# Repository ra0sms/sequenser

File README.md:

# Sequencer

More information - https://ra0sms.com/sequencer-2/

It works in two modes:

1. PA BIAS mode (`MODE` jumper is opened)

2. LNA mode (`MODE` jumper is closed)

--------------------------------------------------------------
PCB dimension: 70*45mm

Consumption current: 30mA

Switch current: up to 1A

### Schematic

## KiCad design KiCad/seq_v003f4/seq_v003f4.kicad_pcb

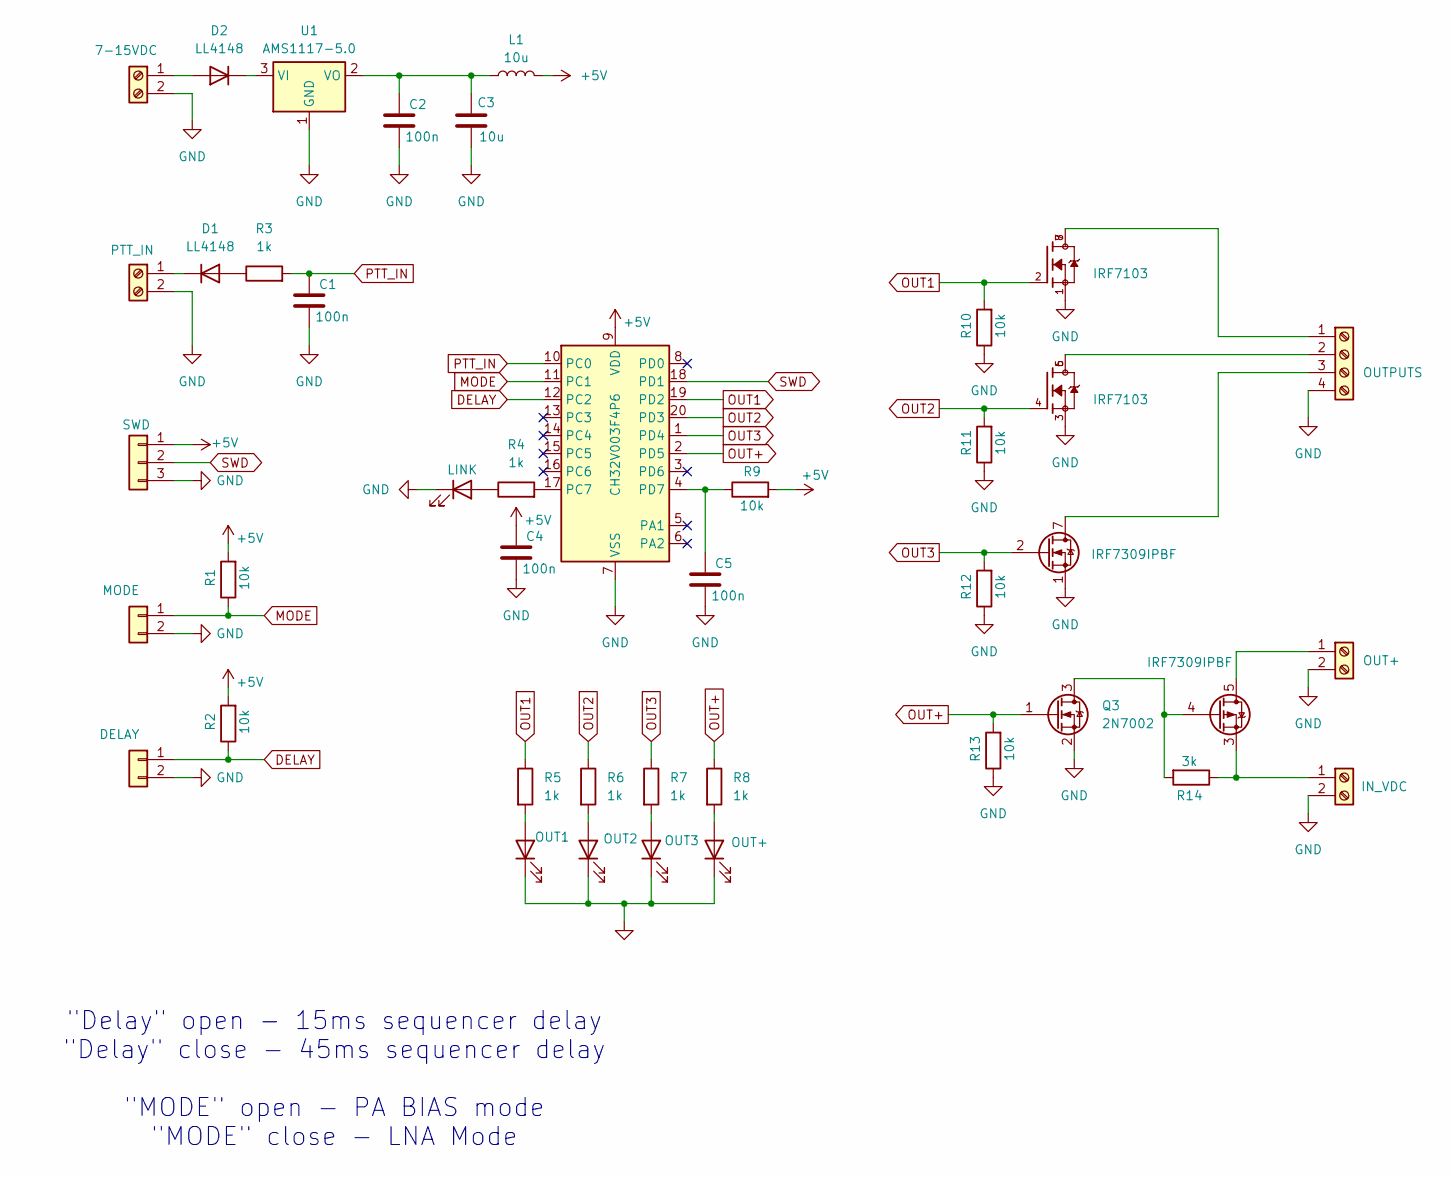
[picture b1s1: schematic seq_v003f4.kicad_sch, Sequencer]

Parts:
C1, C2, C4, C5: 100n; C_1206_3216Metric_Pad1.33x1.80mm_HandSolder
C3: 10u; C_1206_3216Metric_Pad1.33x1.80mm_HandSolder
D1, D2: LL4148; D_MiniMELF
D3: LINK; LED_1206_3216Metric
D4: OUT1; LED_1206_3216Metric
D5: OUT2; LED_1206_3216Metric
D6: OUT3; LED_1206_3216Metric
D7: OUT+; LED_1206_3216Metric
J1: 7-15VDC; TerminalBlock_MetzConnect_Type055_RT01502HDWU_1x02_P5.00mm_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
J2: PTT_IN; TerminalBlock_MetzConnect_Type055_RT01502HDWU_1x02_P5.00mm_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
J3: SWD; PinSocket_1x03_P2.54mm_Vertical
J4: MODE; PinHeader_1x02_P2.54mm_Vertical
J5: DELAY; PinHeader_1x02_P2.54mm_Vertical
J6: OUTPUTS; TerminalBlock_MetzConnect_Type055_RT01504HDWU_1x04_P5.00mm_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
J7: OUT+; TerminalBlock_MetzConnect_Type055_RT01502HDWU_1x02_P5.00mm_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
J8: IN_VDC; TerminalBlock_MetzConnect_Type055_RT01502HDWU_1x02_P5.00mm_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
L1: 10u; L_1206_3216Metric
Q1: IRF7103; SOIC-8_3.9x4.9mm_P1.27mm; PARTREV 02/09/10
Q2: IRF7309IPBF; SOIC-8_3.9x4.9mm_P1.27mm
Q3: 2N7002; SOT-23
R1, R2, R9, R10, R11, R12, R13: 10k; R_1206_3216Metric
R3, R4, R5, R6, R7, R8: 1k; R_1206_3216Metric
R14: 3k; R_1206_3216Metric
U1: AMS1117-5.0; SOT-223-3_TabPin2
U2: CH32V003F4P6; TSSOP-20_4.4x6.5mm_P0.65mm

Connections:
+5V: C4.1, J3.1, L1.2, R1.2, R2.2, R9.2, U2.9 (VDD)
DELAY: J5.1, R2.1, U2.12 (PC2)
GND: C1.2, C2.2, C3.2, C4.2, C5.2, D3.1 (K), D4.1 (K), D5.1 (K), D6.1 (K), D7.1 (K), J1.2, J2.2, J3.3, J4.2, J5.2, J6.4, J7.2, J8.2, Q1.1, Q1.3, Q2.1 (S), Q3.2 (S), R10.1, R11.1, R12.1, R13.1, U1.1 (GND), U2.7 (VSS)
MODE: J4.1, R1.1, U2.11 (PC1)
unnamed: D1.2 (A), R3.1
unnamed: D1.1 (K), J2.1
unnamed: D2.2 (A), J1.1
unnamed: D2.1 (K), U1.3 (VI)
unnamed: D3.2 (A), R4.1
unnamed: D4.2 (A), R5.2
unnamed: D5.2 (A), R6.2
unnamed: D6.2 (A), R7.2
unnamed: D7.2 (A), R8.2
unnamed: J6.1, Q1.7, Q1.8
unnamed: J6.2, Q1.5, Q1.6
unnamed: J6.3, Q2.7 (D), Q2.8 (D)
unnamed: J7.1, Q2.5 (D), Q2.6 (D)
unnamed: J8.1, Q2.3 (1), R14.1
unnamed: Q2.4 (G), Q3.3 (D), R14.2
unnamed: C2.1, C3.1, L1.1, U1.2 (VO)
unnamed: R4.2, U2.17 (PC7)
unnamed: C5.1, R9.1, U2.4 (PD7)
OUT1: Q1.2, R5.1, R10.2, U2.19 (PD2)
OUT2: Q1.4, R6.1, R11.2, U2.20 (PD3)
OUT3: Q2.2 (G), R7.1, R12.2, U2.1 (PD4)
OUT+: Q3.1 (G), R8.1, R13.2, U2.2 (PD5)
PTT_IN: C1.1, R3.2, U2.10 (PC0)
SWD: J3.2, U2.18 (PD1)

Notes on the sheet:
"Delay" open - 15ms sequencer delay "Delay" close - 45ms sequencer delay "MODE" open - PA BIAS mode "MODE" close - LNA Mode

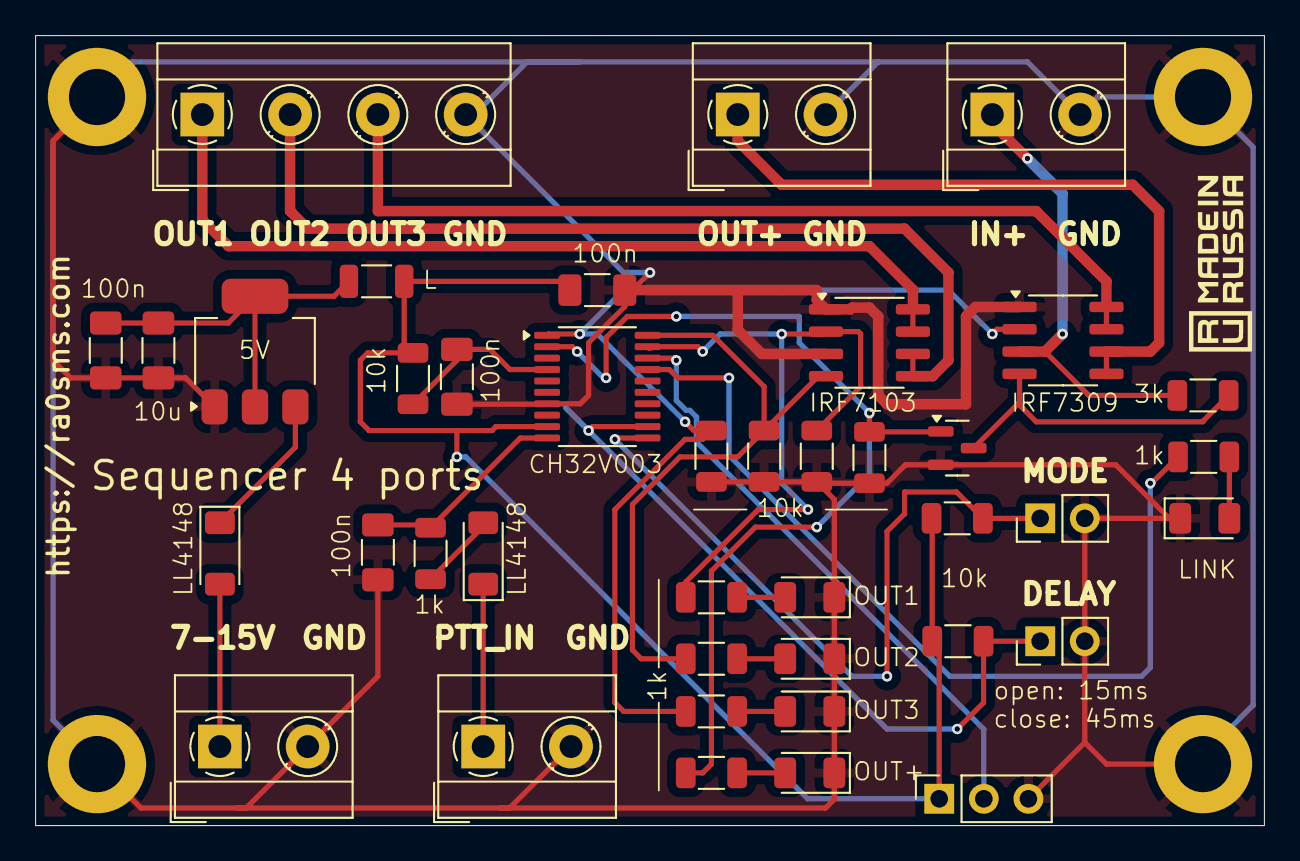
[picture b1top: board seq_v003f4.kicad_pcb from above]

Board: 2 copper layers, 70.0 x 45.0 mm, 40 parts (0 on the bottom side), 28 nets.

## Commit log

2024-08-13 first
2024-08-13 add diagrams
2024-08-14 add pics
2024-08-14 fix start
2024-08-15 add delay after gpio_init
